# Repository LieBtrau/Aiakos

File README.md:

# This project will solve the following problem
When arriving at home  with my bike, I find the garage door still locked.  I have to stop in front of the closed door, take of my backpack, find the keyfob and activate it.  It takes a few seconds then before the door is fully open and I can enter.  When it's raining heavily, every second outside is a second too much.

# Wish
While riding and coming near to my house, press a button on my bike so that the door opens.  By the time I arrive at the door, it's fully open and I can ride in the garage without having to stop on the drive way.

# Solution
The system will consist of three parts:  

* door controller in the garage  
* BLE-enabled key fob in my back pack  
* Wake up initializer  

## Door controller in the garage
The [door controller](https://github.com/LieBtrau/Aiakos/wiki/Garage-controller) is mounted in the garage and connected to the electric motor that can open and close the door.  With its [LoRa](https://www.lora-alliance.org/) module the controller can securely communicate to the key fob.  To make the system operational, the key fob must be paired with the door controller.  The pairing is done by connecting the door controller to the key fob with an audio-jack cable and pressing the button on the key fob.  The serial connection prevents man-in-the-middle (MITM) attacks.  To prevent eavesdropping, the serial connection is secured using [ECDH](https://en.wikipedia.org/wiki/Elliptic-curve_Diffie%E2%80%93Hellman).

## Key fob 
The [key fob](https://github.com/LieBtrau/Aiakos/wiki/Key-fob) is the access token to the system and should be kept safely by the user.  The key fob's Lora module enables communication to the door controller.  The key fob will be asleep most of the time.  When it receives a valid awake command, it will instruct the door controller to open/close the garage door.  The user can wake the key fob in two ways: either by pushing the key fob button, or by pushing the button on the wake up initializer.  
The key fob incorporates a [Bluetooth Low Energy](https://en.wikipedia.org/wiki/Bluetooth_Low_Energy) module to communicate with the wake up initializer.  The key fob will only allow a paired initializer to wake it up.  Pairing involves connecting the fob to the initializer using an audio jack cable and pressing the key fob button.

## Wake up initializer

# Alternatives
## Smartphone and garage controller with WiFi
An off-the-shelf bluetooth tracker is attached to the bike.  The user has a smartphone with a wireless data connection and bluetooth low energy support.  The garage is equipped with an internet connected controller.  After binding the tracker with the smartphone, the system is ready to use.  
Pressing the button on the bluetooth tracker, wakes up the service running on the smartphone.  The smartphone uses geo-location service to check if the smartphone is in the neighbourhood of the garage.  If so, then a command is sent through WiFi to instruct the garage controller to open the door.  
## Smartphone and garage controller with WiFi
The garage controller can be equipped with a bluetooth low energy peripheral IC.  The user could then operate the door using an application on a smartphone.  

*

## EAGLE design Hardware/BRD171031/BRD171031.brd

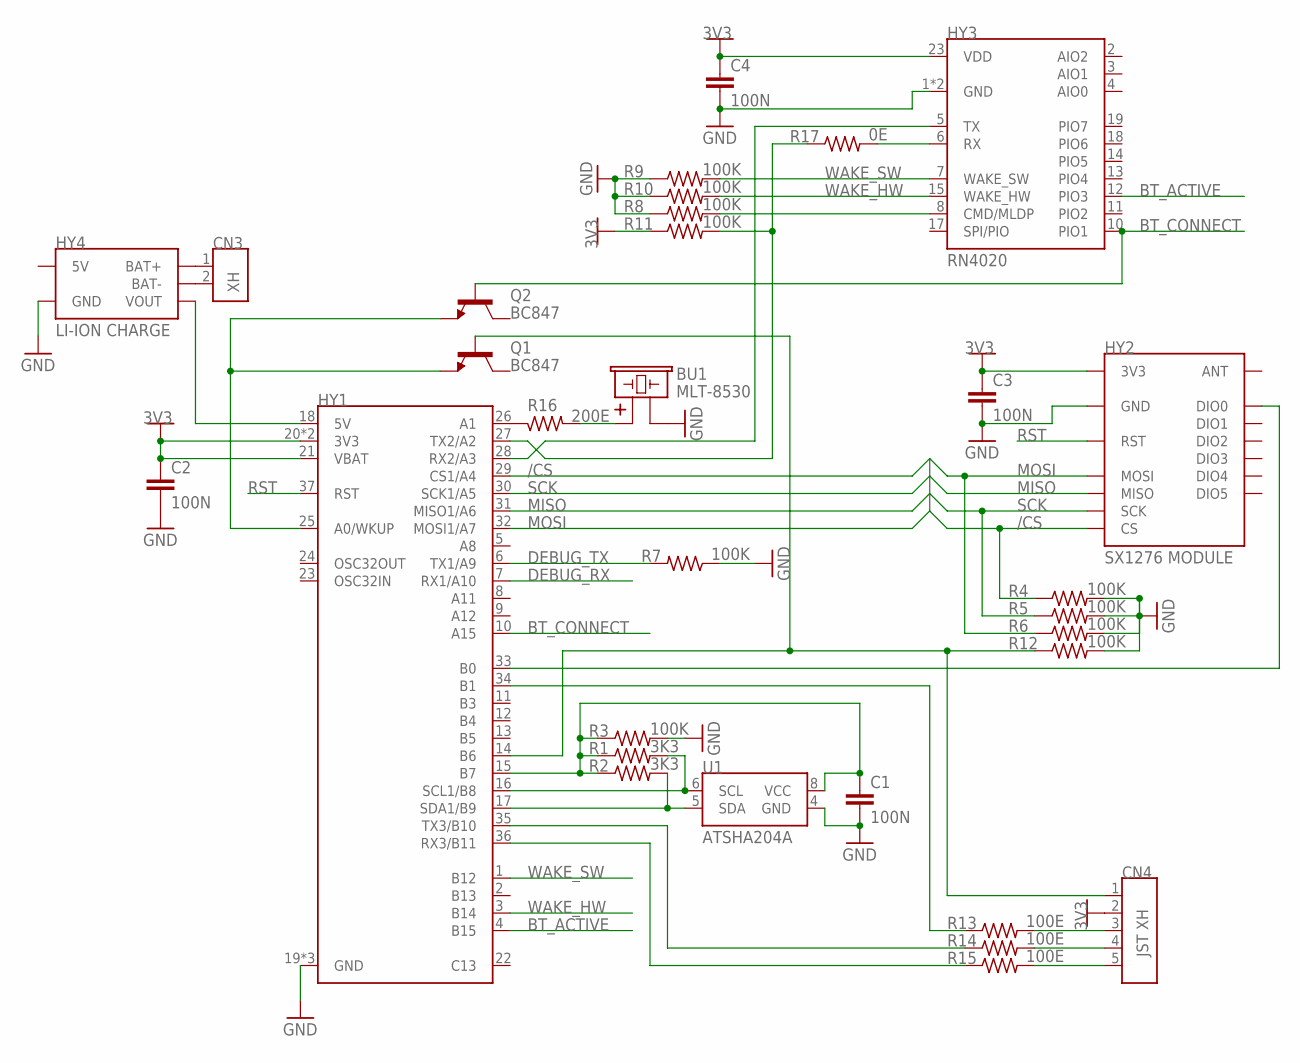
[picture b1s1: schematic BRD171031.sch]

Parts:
BU1: MLT-8530; BU_8530
C1, C2, C3, C4: 100N; CA_1206
CN3: XH; CN_HDR_1X2_180D_P25_JST_B2B-XH
CN4: JST XH; CN_HDR_1X5_180D_P25_JST_B5B-XH
HY1: HY_DEVBRD_BLUEPILL; HY_DEVBRD_BLUEPILL_SMD
HY2: SX1276 MODULE; HY_SX1276
HY3: RN4020; HY_BLE_RN4020
HY4: LI-ION CHARGE; HY_PMMOD_LIION
Q1, Q2: BC847; SC_SOT23
R1, R2: 3K3; RE_1206
R3, R4, R5, R6, R7, R8, R9, R10, R11, R12: 100K; RE_1206
R13, R14, R15: 100E; RE_1206
R16: 200E; RE_1206
R17: 0E; RE_1206
U1: ATSHA204A; SC_SO08

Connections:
3V3: C2.1, C3.1, C4.1, CN4.2, HY1.20 (3V3), HY1.21 (VBAT), HY1.38 (3V3), HY2.VCC (3V3), HY3.23 (VDD), R11.1
/CS: HY1.29 (CS1/A4), HY2.NSS (CS), R4.1
BTN: CN4.1, HY1.14 (B6), Q1.1 (B), R12.1
BT_ACTIVE: HY1.4 (B15), HY3.12 (PIO3)
BT_CONNECT: HY1.10 (A15), HY3.10 (PIO1), Q2.1 (B)
DEBUG_RX: HY1.7 (RX1/A10)
DEBUG_TX: HY1.6 (TX1/A9), R7.2
GND: BU1.2, C1.2, C2.2, C3.2, C4.2, HY1.19 (GND), HY1.39 (GND), HY1.40 (GND), HY2.GND, HY2.GND@1 (GND), HY2.GND@2 (GND), HY3.1 (GND), HY3.24 (GND), HY4.GND1 (GND), HY4.GND2 (GND), R3.2, R4.2, R5.2, R6.2, R7.1, R8.1, R9.1, R10.1, R12.2, U1.4 (GND)
MISO: HY1.31 (MISO1/A6), HY2.MISO
MOSI: HY1.32 (MOSI1/A7), HY2.MOSI, R6.1
unnamed: HY3.6 (RX), R17.2
unnamed: HY1.33 (B0), HY2.DIO0
unnamed: HY1.27 (TX2/A2), R11.2, R17.1
unnamed: HY1.28 (RX2/A3), HY3.5 (TX)
unnamed: HY3.8 (CMD/MLDP), R8.2
unnamed: HY1.36 (RX3/B11), R15.1
unnamed: HY1.35 (TX3/B10), R14.1
unnamed: HY1.34 (B1), R13.1
unnamed: HY1.25 (A0/WKUP), Q1.2 (E), Q2.2 (E)
unnamed: HY1.26 (A1), R16.1
unnamed: CN4.3, R13.2
unnamed: CN4.4, R14.2
unnamed: CN4.5, R15.2
unnamed: BU1.1, R16.2
unnamed: HY1.18 (5V), HY4.OUT+ (VOUT)
unnamed: CN3.1, HY4.B+ (BAT+)
unnamed: CN3.2, HY4.B- (BAT-)
PWR_U1: C1.1, HY1.15 (B7), R1.1, R2.1, R3.1, U1.8 (VCC)
RST: HY1.37 (RST), HY2.REST (RST)
SCK: HY1.30 (SCK1/A5), HY2.SCK, R5.1
SCL: HY1.16 (SCL1/B8), R1.2, U1.6 (SCL)
SDA: HY1.17 (SDA1/B9), R2.2, U1.5 (SDA)
WAKE_HW: HY1.3 (B14), HY3.15 (WAKE_HW), R10.2
WAKE_SW: HY1.1 (B12), HY3.7 (WAKE_SW), R9.2

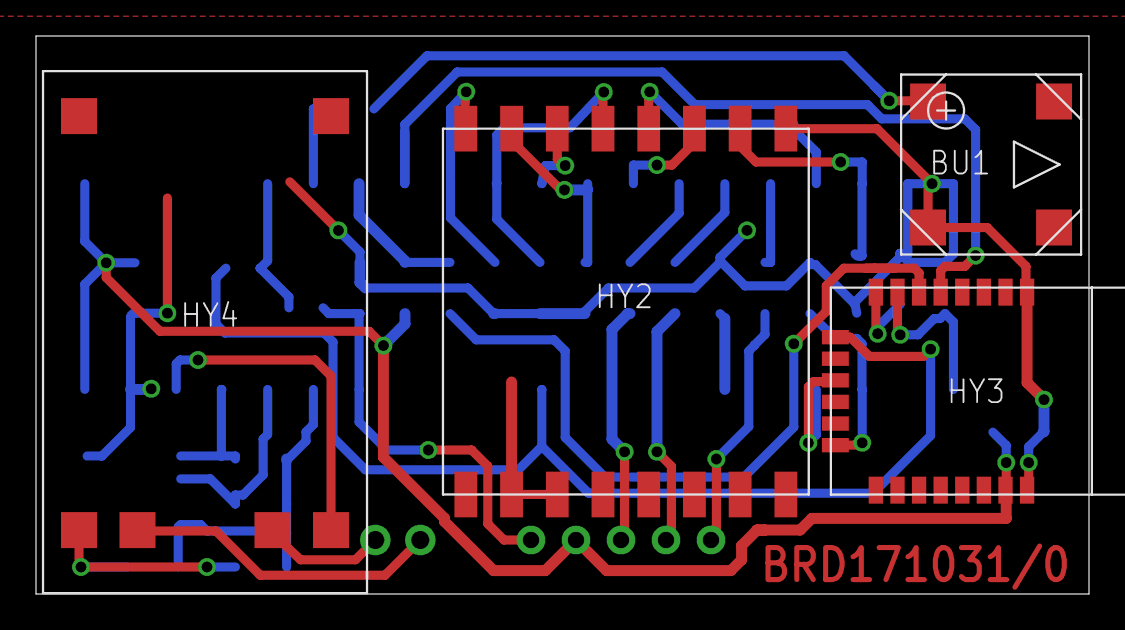
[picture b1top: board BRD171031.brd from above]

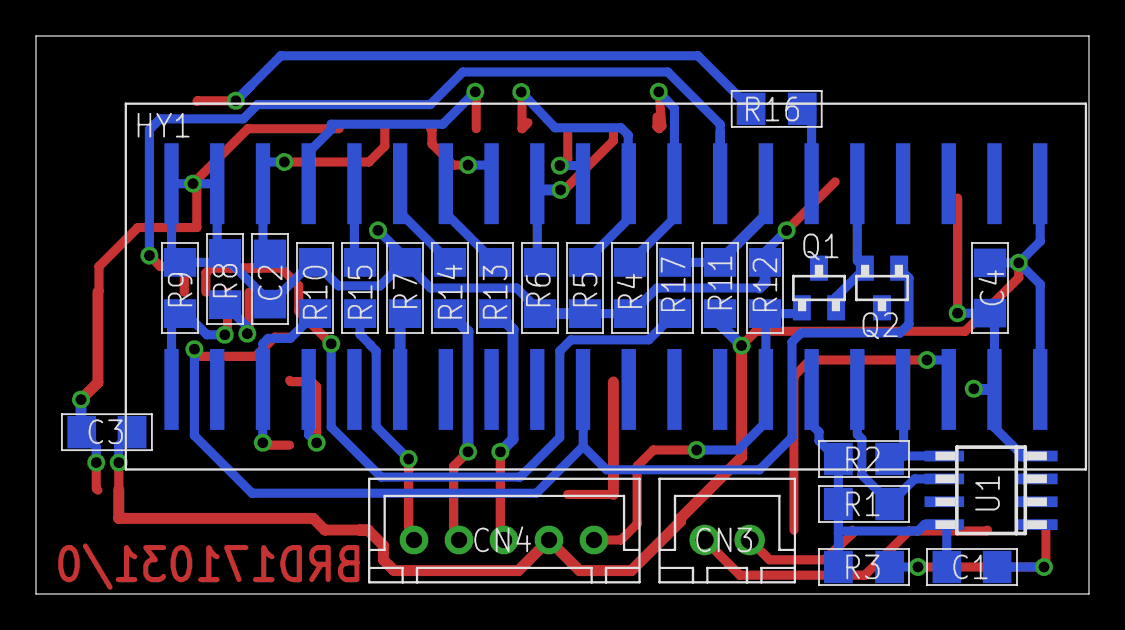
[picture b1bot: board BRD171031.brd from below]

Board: 2 copper layers, 58.5 x 31.0 mm, 32 parts (27 on the bottom side), 33 nets.

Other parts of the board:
U$2: MC_FRAME_A5

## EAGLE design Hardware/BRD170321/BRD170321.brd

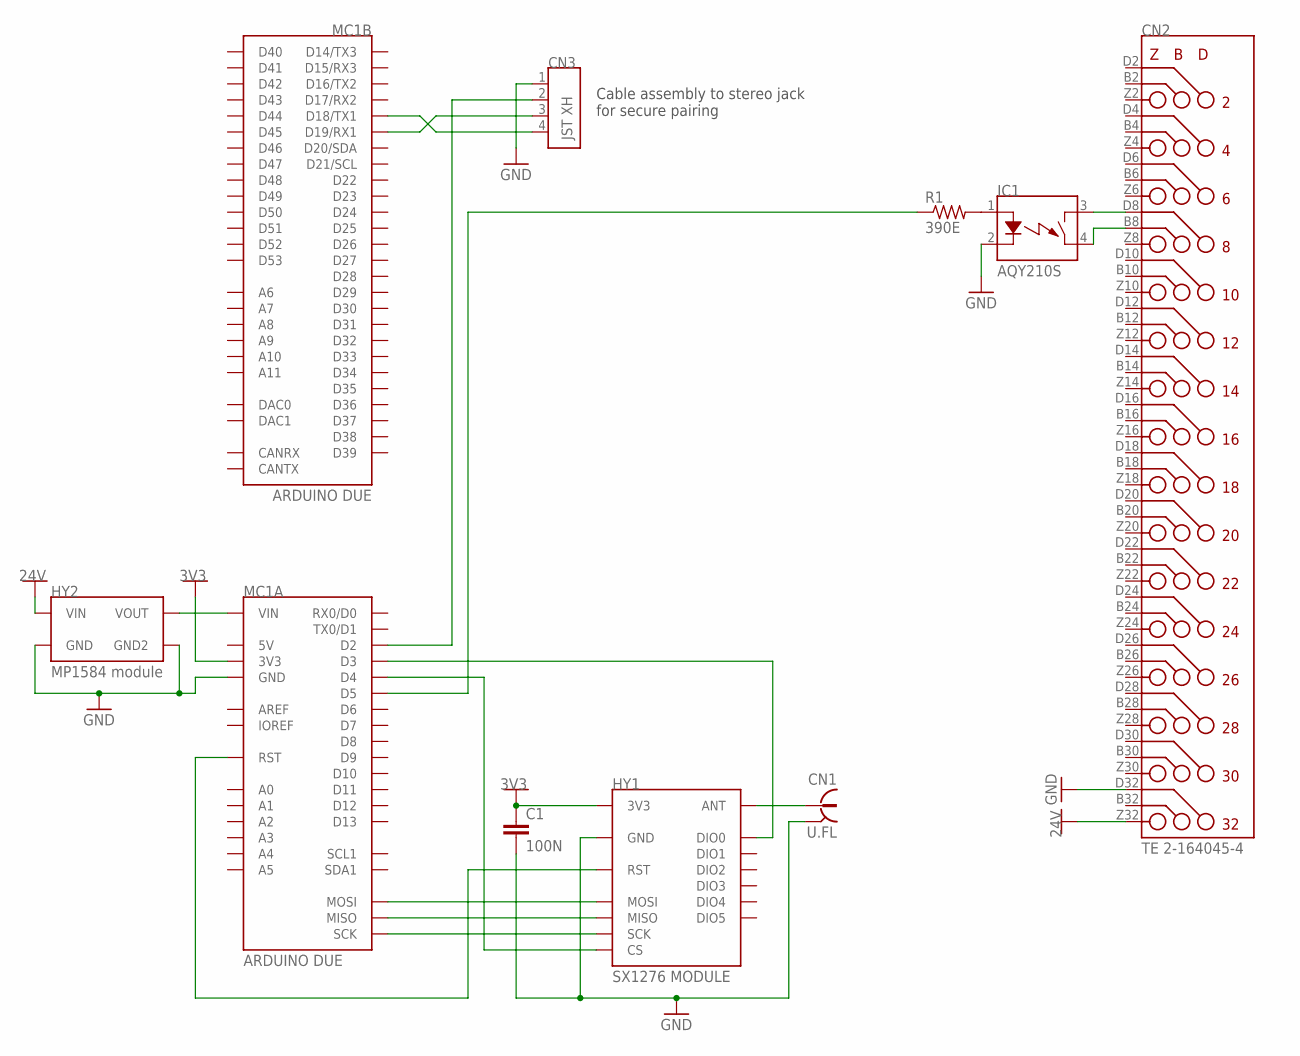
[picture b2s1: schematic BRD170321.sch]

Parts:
C1: 100N; CA_1206
CN1: U.FL; CN_RF_U.FL_MALE
CN2: TE 2-164045-4; CN_HDR_DIN41612F_90D
CN3: JST XH; CN_HDR_1X4_180D_P25_JST_B4B-XH
HY1: SX1276 MODULE; HY_SX1276
HY2: MP1584 module; HY_MP1584
IC1: AQY210S; SC_SO6_P4
MC1: ARDUINO DUE; MC_ARDUINO_DUE
R1: 390E; RE_1206

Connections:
3V3: C1.1, HY1.VCC (3V3), MC1.3.3V (3V3)
24V: CN2.Z32 (32Z), HY2.IN+ (VIN)
GND: C1.2, CN1.2A (OUTER), CN1.2B (OUTER), CN2.D32 (32D), CN3.1, HY1.GND, HY1.GND@1 (GND), HY1.GND@2 (GND), HY2.IN- (GND), HY2.OUT- (GND2), IC1.2 (C), MC1.GND@1 (GND), MC1.GND@2 (GND), MC1.GND@3 (GND), MC1.GND@4 (GND), MC1.GND@5 (GND), MC1.GND@6 (GND)
unnamed: IC1.1 (A), R1.2
unnamed: CN1.1 (INNER), HY1.ANT
unnamed: HY1.MOSI, MC1.MOSI
unnamed: HY2.OUT+ (VOUT), MC1.VIN
unnamed: CN2.D8 (8D), IC1.3 (D1)
unnamed: CN2.B8 (8B), IC1.4 (D2)
unnamed: MC1.5 (D5), R1.1
unnamed: HY1.MISO, MC1.MISO
unnamed: HY1.SCK, MC1.SCK
unnamed: HY1.NSS (CS), MC1.4 (D4)
unnamed: HY1.DIO0, MC1.3 (D3)
unnamed: HY1.REST (RST), MC1.RESET (RST), MC1.RESET@2 (RST)
unnamed: CN3.2, MC1.2 (D2)
unnamed: CN3.3, MC1.19 (D19/RX1)
unnamed: CN3.4, MC1.18 (D18/TX1)

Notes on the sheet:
Cable assembly to stereo jack for secure pairing

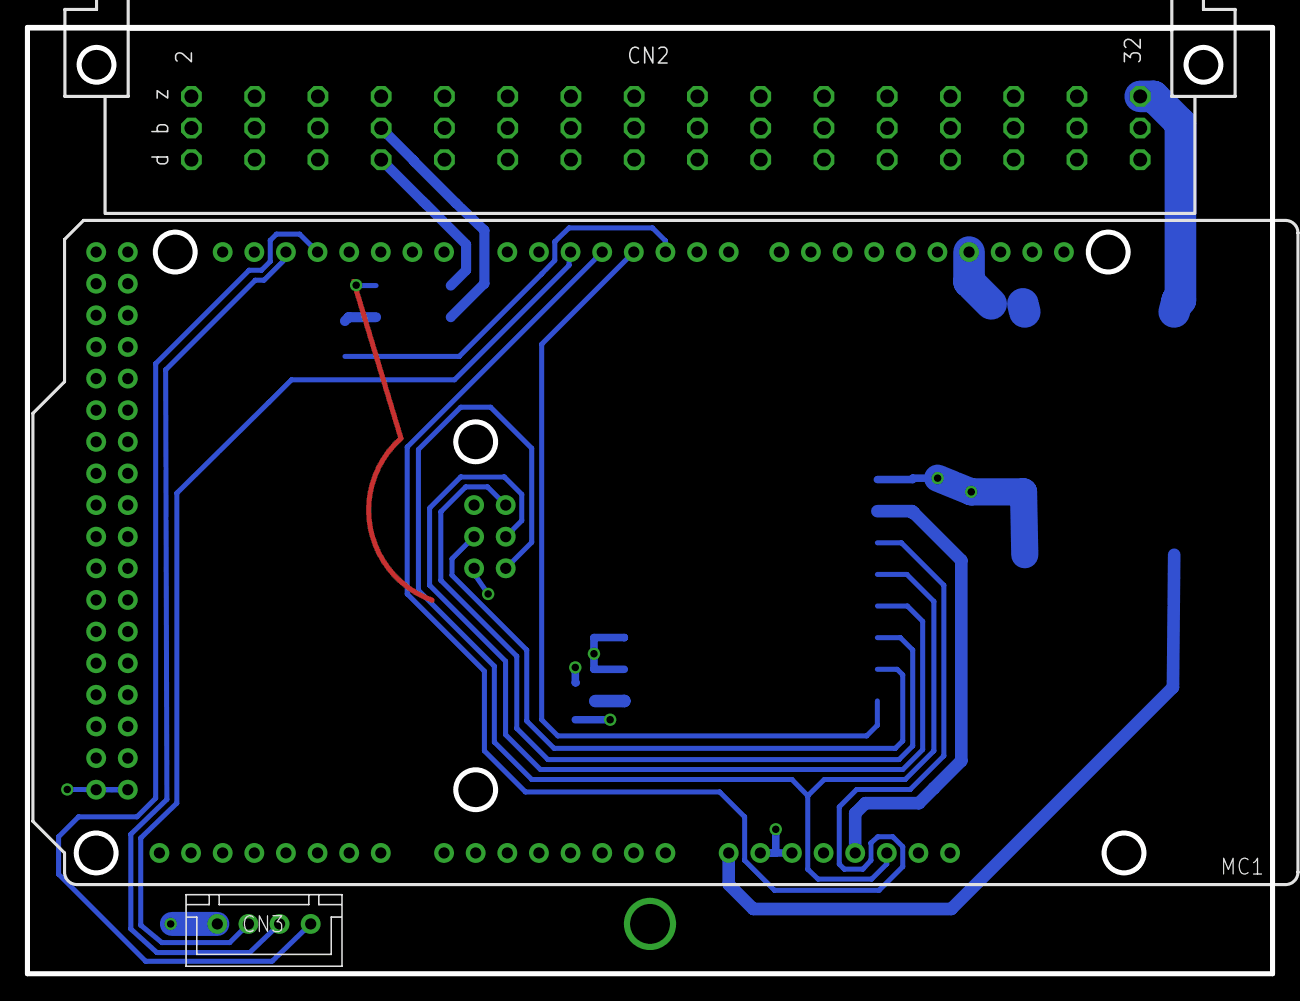
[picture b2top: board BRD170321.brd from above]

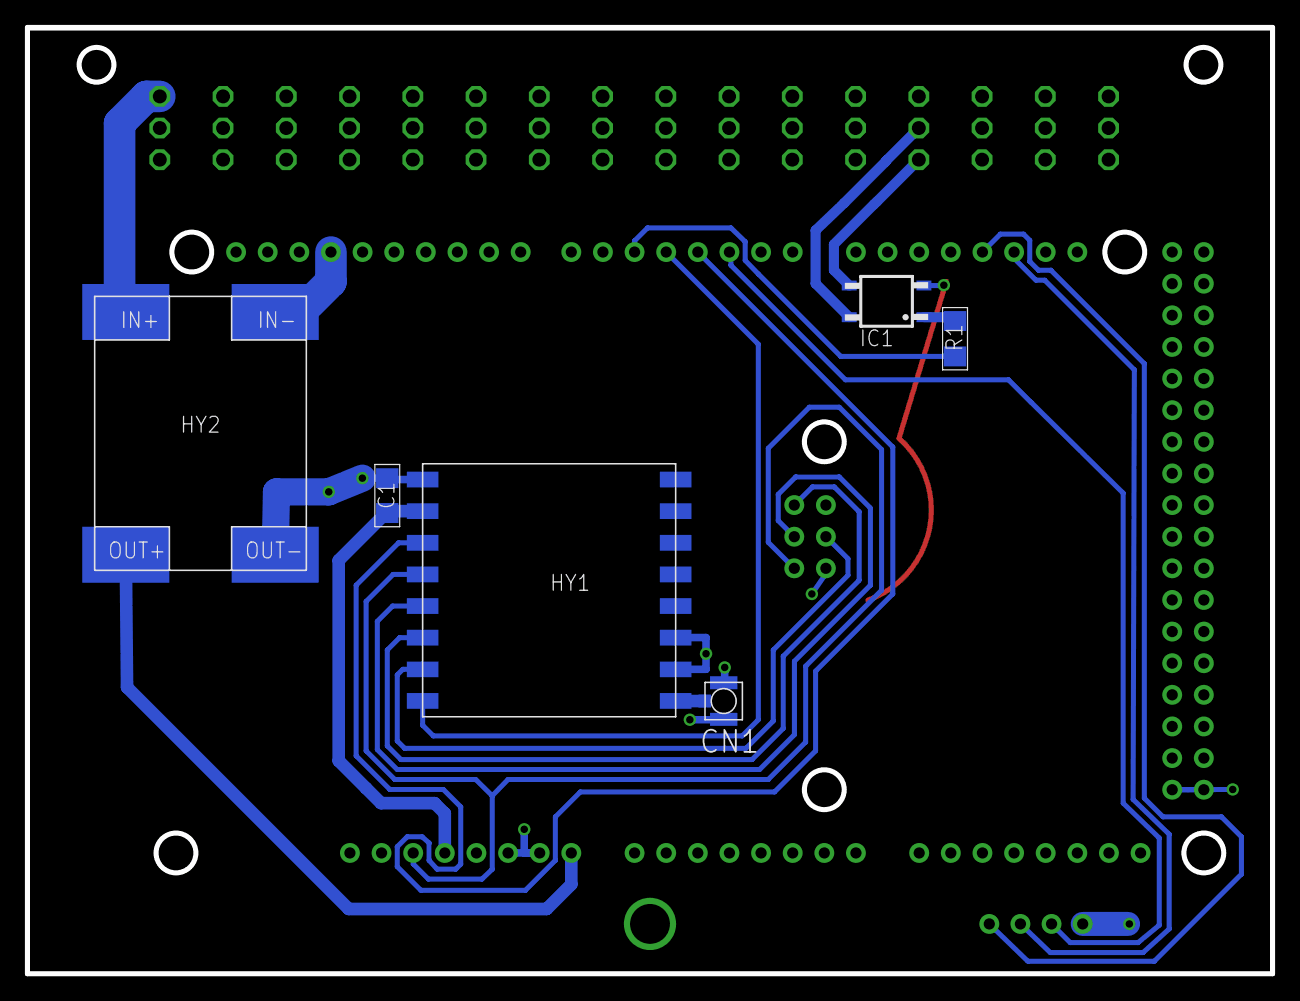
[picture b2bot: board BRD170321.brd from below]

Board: 2 copper layers, 100.0 x 76.0 mm, 11 parts (6 on the bottom side), 18 nets.

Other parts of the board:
DRILEGEND: DRILEGEND
U$6: MC_FRAME_A5

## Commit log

2014-08-30 Version with working RFID reading.
2014-08-30 Adding a readme
2014-08-30 Adding a license
2014-10-06 Adding the Wireless driver
2014-10-08 Setting RFID in separate library
2014-10-09 Adding rfid library
2014-10-09 Restoring rdm630 library to its original form Code doesn't build yet because USER_LIB_PATH is not yet set correctly.
2014-10-10 No code changes, everything compiles now.
2014-10-10 Working RFID
2014-10-11 Updating documentation
2014-10-13 Adding info on how to implement the firmware
2014-10-21 Adding the ATECC108 library, but it doesn't compile yet. Also some updates to the readme.md file.
2014-10-22 Busy implementing I²C, but removing the physical layer
2014-10-23 Compiling ok.
2014-10-25 Firmware compiles with one example enabled.
2014-10-25 This firmware is capable of waking up the device.
2014-10-26 First working example
2014-10-29 Working version of ATECC108
2014-11-02 Fixing bug: word_address was not sent in commands Read info now returns valid info. Still doesn't know what it means though.
2014-11-04 Working example of checkMAC
2014-11-09 First files of simple usage class implemented: MAC generation & verification works.
2014-11-12 Adding readout of serial number of the device, based on EClet code.
2014-11-22 check-in prior to swapping ATECC108 library for ATSHA204 library
2014-11-22 removing ATECC108 library
2014-11-22 removing Wire2 library (it was only used by ATECC108)
2014-11-24 Working example for reading the serial number of the ATECC108/SHA204
2014-11-24 Adding Wire2 library again. The standard Wire library has too small buffers.
2014-11-29 Reading full config zone implemented (command will enable to verify if writing config command works well)
2014-12-01 Writing config succeeded
2014-12-02 Writing config zone: added setting OTP zone mode.
2014-12-14 Adding IrDA, sending byte works
2014-12-15 IrDA: sending multiple bytes works
2014-12-16 IrDA sending: ASYNC wrapper implemented
2014-12-21 IrDA Receiving: measuring time between rising edges works
2014-12-21 IrDA: reception of multiple bytes works offline (lots of debugging info is on)
2014-12-27 Offline receiving of IrDA codes works.
2014-12-27 Working example of offline decoding IrDA data
2014-12-30 IrDA: working online decoding
2014-12-30 IrDA: online receiving and decoding works
2015-01-03 IrDA: Working online decoding with circular buffer filling
2015-01-04 Updating comments, cleaning up debug messages
2015-01-04 For sending IrDA, now also use Timer1 (instead of Timer2), so that this whole library needs only one timer.
2015-01-04 Continuously reading from ringbuffer and showing result
2015-01-05 Solving bug: a spurious input capture interrupt was generated when switching from sending to receiving.
2015-01-05 Fixing bug: first character of 2nd and following packages never got sent.
2015-01-05 Working IrDa "chat"-application (however, no HW-chips used, communication goes using wires)
2015-01-06 Working chat application with raw IR-data
2015-01-11 Working IrDA chat application with ASYNC-wrapper
2015-06-15 last commit before moving
2015-06-15 moving to folder Atmel
2015-06-15 Adding Nucleo project
2015-06-15 updating view
2015-06-16 Adding RSSI measurement during scanning
2015-06-19 reading address, address type and RSSI works
2015-06-20 solving bug in getting RSSI
2015-06-21 Implementing unbounding + connecting
2015-06-23 Bounding procedure and connecting works + keeping connection open.
2015-07-19 serial passthrough mode implemented for easier RN4020 debug
2015-07-19 Moving info to wiki
2015-07-19 using relative links
2015-09-12 Removing RadioHead library, because it has been moved to a separate repository.
2015-09-12 Adding temporary development files
2015-09-13 NFC reading works with Arduino Due
2015-09-13 Adding build instructions
2015-09-13 Testing Wireless communication
2015-09-15 Enabling NFC and wireless communication simultaneously.
2015-09-17 Removing ST folder because development on STM32 continues in Nucleo folder.
2015-09-29 Adding block write and block read routines for EEPROM, to enable compatibility on MicroBox with AVR
2015-09-30 Fixing reading EEPROM for uneven numbered sizes.
2015-10-04 Adding info about standalone use of keyfob
2015-10-14 ECDH Test application with a keypair stored in flash in base64 format and a keypair generated on the fly Signed-off-by: Christoph Tack <prog.send@gmail.com>
2015-10-19 Adding CMAC functionality
2015-10-24 Working NFC-SEC01 master key calculation
2015-10-24 NFC-SEC 01: Key Agreement, Derivation and Confirmation implemented and tested.
2015-12-13 Updating readme
2015-12-20 Adding working NDEF tag functionality
2015-12-20 Adding Ntag Sram adapter
2015-12-22 Adding function to release the I²C-bus when it's stuck.
2015-12-22 Data stored in NDEF as unknown record.
2015-12-24 Working application of reader and tag sending messages to each other (running on one MCU)
2015-12-24 Moving crypto files to a separate library
2016-01-03 Build works for Nucleo on Arduino 1.6.5 Build works for Arduino Due on Arduino 1.6.7
2016-01-03 Working version of sending data back and forth through RF interface
2016-01-03 Moving authentication to separate class.
2016-01-04 development in progress
2016-01-11 working without crash
2016-01-13 security copy, not yet functional
2016-01-18 Working version of NFC pairing, timing can be better though.
2016-01-25 Working NFC authentication
2016-04-22 Adding kryptoknight authentication to project
2016-07-25 Adding RN4020 interface
2016-08-02 RN4020 implementation
2016-08-04 Addin private characteristics works
2016-08-25 Application with BLE and RFID (not enabled)
2016-09-04 Finding remote devices works
2016-09-05 Adding new solution for this problem
2016-09-05 Parsing advertizements works
2016-09-11 Getting bonding parameters from RN4020 works
2016-09-13 Bonding and rebonding works
2016-09-15 Adding ProTrinket build & run settings to project
2016-10-19 half implemented
2016-10-19 First working LoRa test
2016-10-19 Reliable communication implemented with two ProTrinkets
2017-01-20 RadioHead fix for NucleoF103RB
2017-01-28 Implementing LoRa into own application
2017-01-28 Adding wired serial port support
2017-01-31 implementing initiator key agreement
2017-02-01 Implementing key agreement. It's too heavy for the ATMEGA328
2017-02-08 Authenticated wireless transfer works, kryptoknight implemented.
2017-02-21 Wireless communication doesn't work well.
2017-02-21 version with working wireless communication
2017-02-21 Fixed wireless communication with authentication
2017-02-23 Putting back old comments
2017-02-28 Secure pairing implemented according nfc-sec
2017-03-05 Secure pairing over serial port works
2017-03-05 Secure pairing (wired) and authentication (wireless) are both working
2017-03-05 Making clear that smartphone is not an option
2017-03-07 EEPROM implemented. To be tested.
2017-03-08 Working: * secure pairing with storage of key to EEPROM * reading key from EEPROM and using it for sending authenticated text.
2017-03-09 Implementing crypto functions for Arduino Due Compilation for Due and Nucleo OK, but not tested.
2017-03-12 Fixing bug
2017-03-12 Working version
2017-03-17 cryptohelpers implemented and tested with secure pairing and authenticated text
2017-03-19 role Due = garage controller role Nucleo = key fob
2017-03-19 Findkey instead of findkeyindex
2017-03-19 Cleaning up configuration interface
2017-03-20 Garage controller and key fob have their own loop(). Pairing and authenticating with stereo cable detect works.
2017-03-29 Moving code to "Firmware" folder
2017-03-29 BRD170321 R00.0x
2017-04-03 Restoring readme
2017-04-03 Reorganizing project
2017-04-03 Adjusting to new markdown
2017-04-23 Working application for garage controller. All functionality implemented. Debugging enabled
2017-04-24 Fixing bug in storage address of default key
2017-04-24 Removing Eagle output from repository
2017-04-30 -Disabling peripherals clocks -Switching CPU speeds at runtime
2017-05-01 Further reducing MCU speed in wait mode
2017-05-01 updating link to garage controller
2017-05-02 Adding pictures
2017-05-10 Sketch uses 41,964 bytes (8%) of program storage space. Maximum is 524,288 bytes.
2017-05-11 running code on key fob
2017-05-12 Cleaning up. Code works ok.
2017-06-18 Removing peerAddress from constructor
2017-06-18 opened with a newer version of Eagle
2017-06-29 Adding project for ProTrinket 3V
2017-07-23 Migrating from Nucleo to Blue Pill full functionality works.
2017-08-08 Build ok
2017-08-15 Ble pairing works more or less
2017-08-16 Ble bonding works
2017-08-20 Improving pairing & characteristic writes
2017-08-20 Write multiple bytes to characteristic
2017-09-02 bug fix on sscanf adding findMe
2017-09-05 -Functioning pairing between keyfob & bike -Functioning generating of BLE-event with sending & checking RFID key
2017-09-09 Firmware as programmed in installed garage-controller
2017-09-09 Improving MCU speed control
2017-09-19 Speeding up booting of Blue Pill
2017-09-24 bug fix with sizeof() rfid key size length now depends on a constant
2017-09-28 Pairing and remote rfid sending works
2017-10-03 Working sleep functionality in main class
2017-10-10 Fixing GarageController
2017-10-10 Code as programmed in the GarageController
2017-10-10 Adding build options
2017-10-13 Enabling wake-up from BLE
2017-10-17 detecting wakeup sources
2017-10-21 fixing alert level
2017-10-29 Applying low power to the LoRa module and crypto device
2017-10-29 -cleaning up advertizing code -push button now active high (saves an inverter) -push button detection moved to other pin (for low current purposes)
2017-11-21 Add VCC-reading
2017-11-29 Pin swaps for easier PCB layout
2017-11-29 Adding keyfob R00.00
2018-03-25 Minor improvements after completing key fob hardware
2020-09-24 Adding zip to gitignore
2020-09-24 Simple micropython web server
2020-09-27 web server on SSL with pin code reading
2020-09-28 web server checks pin code & responds accordingly
2020-10-02 Adding garage door impulse output
2021-11-26 Fixing self-signed certificate
2021-11-27 adding readme
2022-06-05 Updating comments
